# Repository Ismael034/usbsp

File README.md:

# USBsp

Have you ever tried to plug a USB device into a computer that has USB restrictions enabled? It's frustrating, isn't it? You can't use your USB devices, and you have no way to bypass the restrictions. But what if I told you that you could spoof the USB identifiers so you bypass these restrictions? That's where USBsp comes in.

Here is your solution!

USBsp is a USB device that can spoof the USB identifiers of any device you want. It is based on the CH32V203 and CH572D microcontrollers. With USBsp, you can easily bypass USB restrictions and use your USB devices without any issues.

## Features

- Spoofs basic USB descriptor fields: VID, PID, bcdDevice, manufacturer, product and serial.
- Stores the spoofed descriptor settings in EEPROM.
- WebUSB control panel for changing settings from a Chromium-based browser.
- Can read descriptor-like values from the currently connected downstream USB device and use them as a starting point.
- Basic live packet capture.
- Simple HID keyboard/mouse visualizers.

## Building

The required toolchain is alredy included. It is a custom toolchain made by WCH, downloaded from [here](https://www.mounriver.com/download). This toolchain constains custom targets for their MCUs. Other toolchains (like xpack) have not been tested.

### Clone the repository and add the toolchain to the path

```
git clone https://github.com/Ismael034/usbsp.git
cd usbsp
export PATH=$PWD/toolchain/bin/:$PATH
```

### Configure meson

```
meson setup build-ch32v203 --cross-file ch32v203/ch32v203-cross.ini
meson setup build-ch572d --cross-file ch572d/ch572d-cross.ini
```

### Build with ninja

```
ninja -C build-ch32v203 ch32v203/ch32v203.hex
ninja -C build-ch572d ch572d/ch572d.hex
```

If everything goes well, you'll end up with two .hex files – one for each MCU.

## Flashing

To flash the firmware to your MCU, you can use one of the following tools:

- [WCH-LinkUtility](https://www.wch.cn/downloads/wch-linkutility_zip.html)
- [wlink](https://github.com/ch32-rs/wlink/)
- [OpenOCD](https://openocd.org/)

```
wlink flash ./build-ch32v203/ch32v203/ch32v203.hex
wlink flash ./build-ch572d/ch572d/ch572d.hex
```

## Tests

It is also possible to build a test firmware, which will test hardware funcionality like EEPROM access, USBD, USBH, buttons, etc. You can build it using a predefined custom target.

```
ninja -C build-ch32v203 ch32v203/ch32v203_test.hex
```

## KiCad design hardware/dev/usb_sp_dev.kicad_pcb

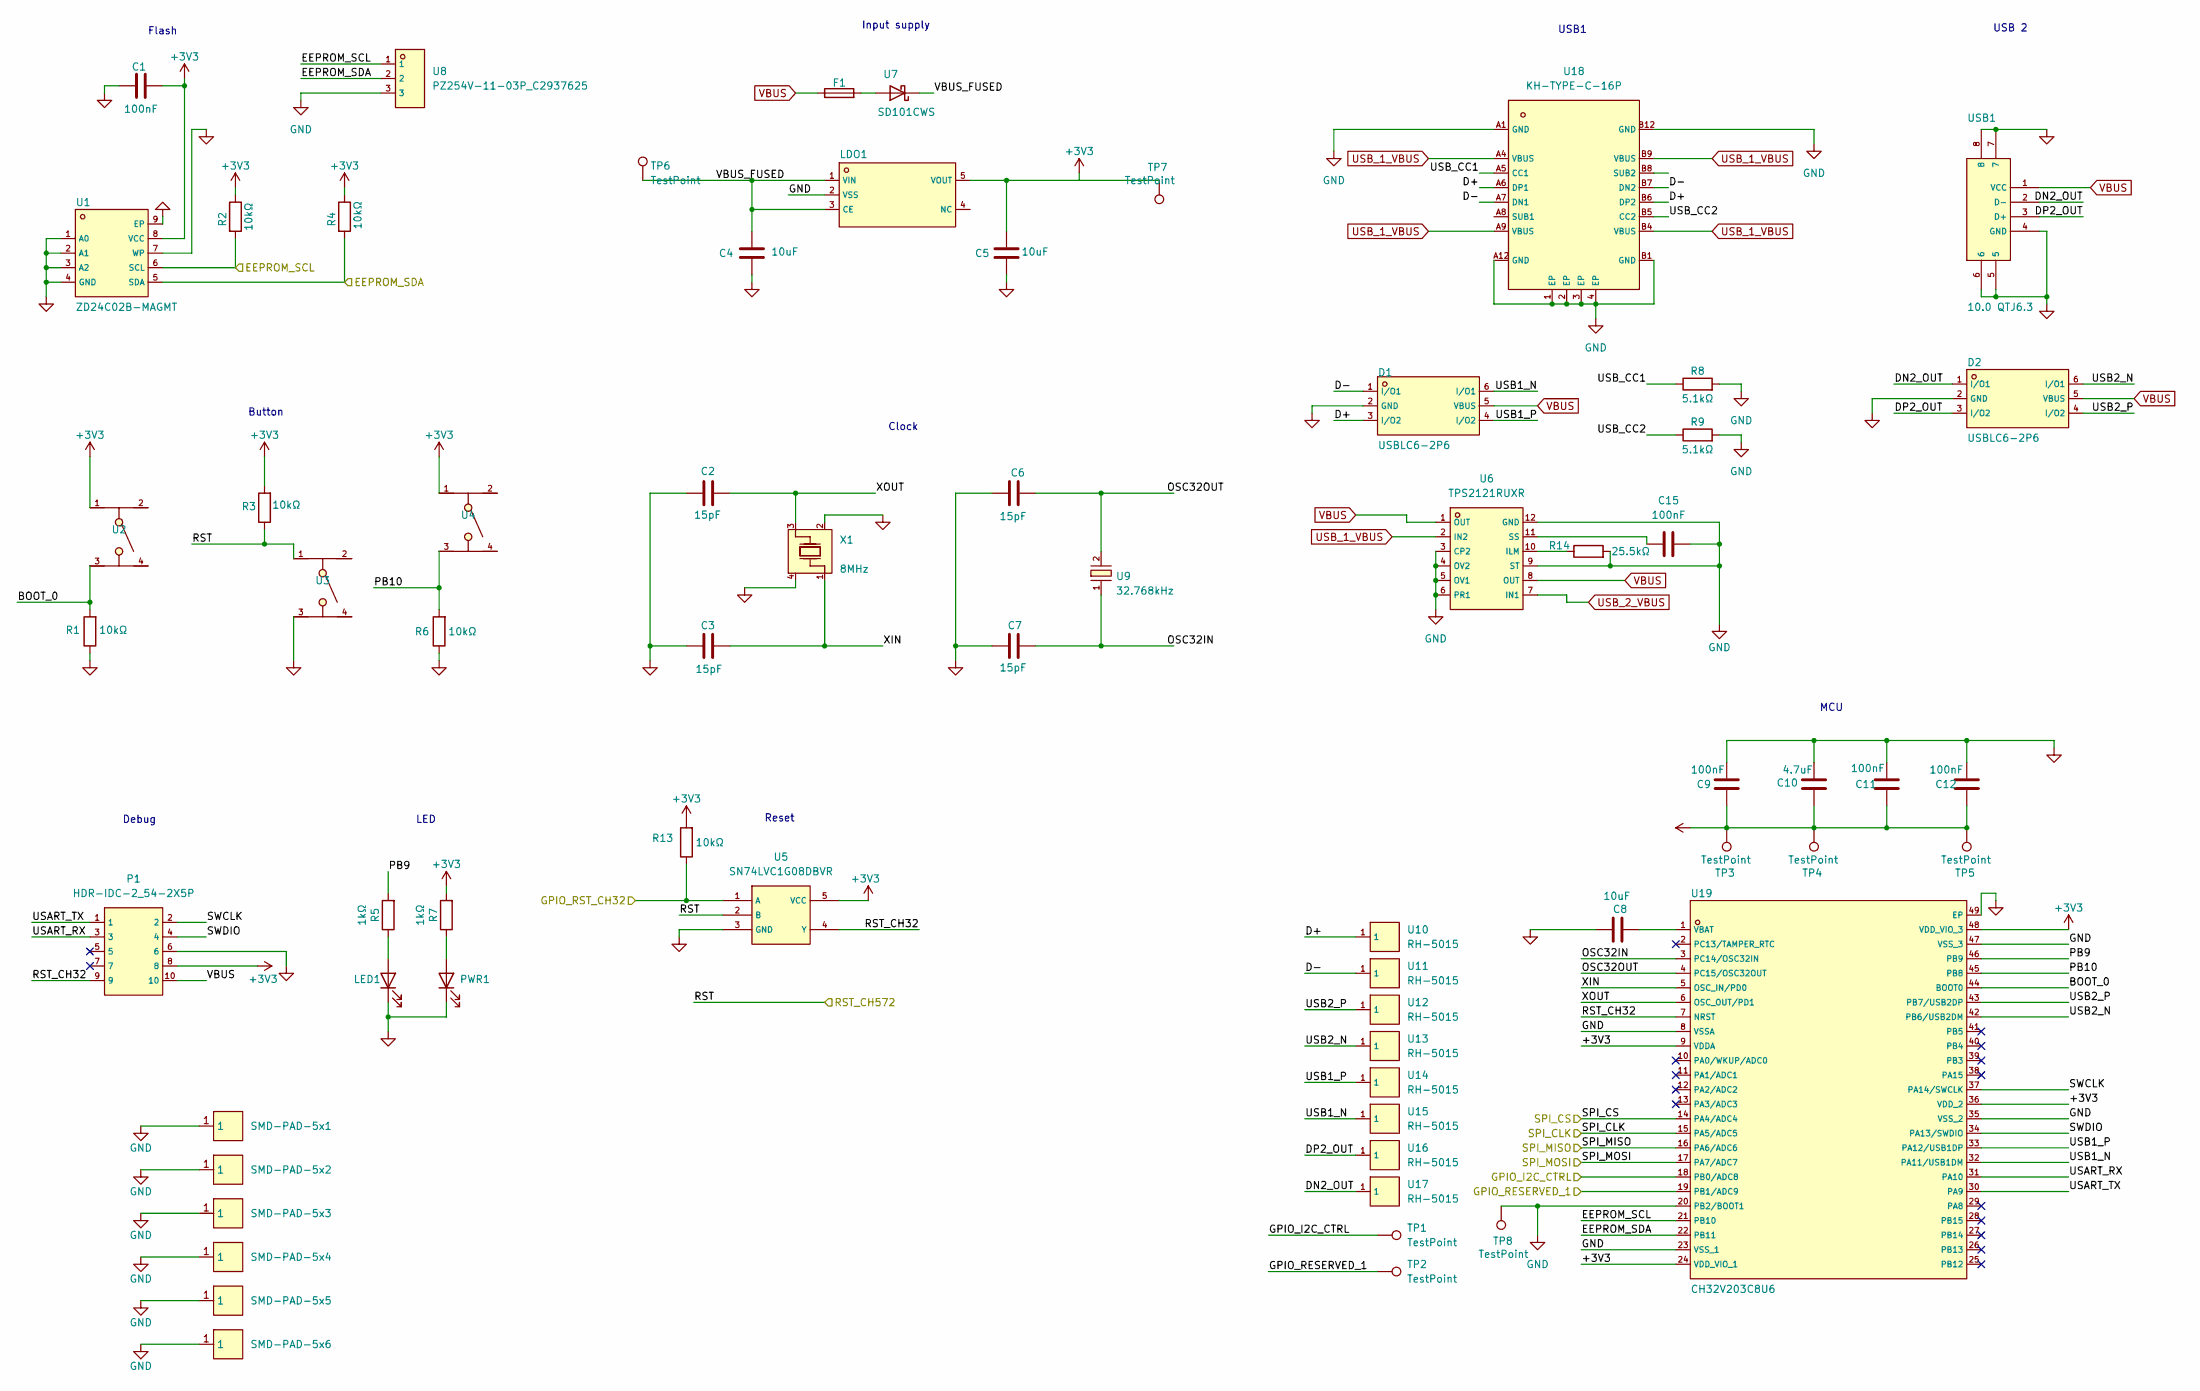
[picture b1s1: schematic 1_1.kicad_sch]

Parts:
C1: 100nF; C_0402_1005Metric; Manufacturer Part CL05B104KO5NNNC; LCSC Part Name 100nF ±10% 16V
C2, C3, C6, C7: 15pF; C_0402_1005Metric; Manufacturer Part 0402CG150J500NT; LCSC Part Name 15pF ±5% 50V
C4, C5, C8: 10uF; C_0603_1608Metric; Voltage Rating 10V; Manufacturer Part CGA0603X5R106K100JT; LCSC Part Name 10uF ±10% 10V
C9, C11, C12: 100nF; C_0603_1608Metric; Manufacturer Part CGA0603X7R104K500JT; LCSC Part Name 100nF ±10% 50V
C10: 4.7uF; C_0603_1608Metric; Manufacturer Part CL10A475KP8NNNC; LCSC Part Name 4.7uF ±10% 10V
C15: 100nF; C_0603_1608Metric
D1, D2: USBLC6-2P6; SOT-666-6_L1.6-W1.2-P0.50-LS1.6-BL; Manufacturer Part USBLC6-2P6; LCSC Part Name MSL=3
F1: JK-SMD0805-020-30V; Fuse_0805_2012Metric; Manufacturer Part JK-SMD0805-020-30V; LCSC Part Name 30V 200mA 0805自恢复
LDO1: ME6211C33M5G-N; SOT-23-5_L3.0-W1.7-P0.95-LS2.8-BL; Manufacturer Part ME6211C33M5G-N; LCSC Part Name 输入6V 输出3.3V 500mA
LED1: XL-1608UGC-04; LED_0603_1608Metric; Manufacturer Part XL-1608UGC-04; LCSC Part Name XL-1608UGC-04
P1: HDR-IDC-2_54-2X5P; IDC-TH_10P-P2.54_C5665; LCSC C5665
PWR1: NCD0603R1; LED_0603_1608Metric; Manufacturer Part NCD0603R1; LCSC Part Name NCD0603R1
R1, R2, R3, R4, R6, R13: 10kΩ; R_0603_1608Metric; Manufacturer Part RC0603JR-0710KL; LCSC Part Name 厚膜电阻 10kΩ ±5% 100mW
R5, R7: 1kΩ; R_0603_1608Metric
R8, R9: 5.1kΩ; R_0603_1608Metric
R14: 25.5kΩ; R_0603_1608Metric
SMD-PAD-5x1, SMD-PAD-5x2, SMD-PAD-5x3, SMD-PAD-5x4, SMD-PAD-5x5, SMD-PAD-5x6: SMD-PAD-5x5
TP1, TP2, TP3, TP4, TP5, TP6, TP7, TP8: TestPoint; TestPoint_Pad_D1.0mm
U1: ZD24C02B-MAGMT; UDFN-8_L3.0-W2.0-P0.50-BL-EP-3; Manufacturer Part ZD24C02B-MAGMT; LCSC Part Name 2Kbit I2C兼容串行EEPROM
U2, U3, U4: TC-6601-5_0-260-8_3; SW-SMD_4P-L6.0-W6.0-P4.50-LS8.2; Manufacturer Part TS-1088-AR02016; LCSC Part Name 4*3*2mm 立贴 轻触开关
U5: SN74LVC1G08DBVR; SOT-23-5_L3.0-W1.7-P0.95-LS2.8-BR; LCSC C7666
U6: TPS2121RUXR; VQFN-HR-12_L2.5-W2.0-P0.50-BL; LCSC C485916
U7: SD101CWS; D_SOD-323; Manufacturer Part SD101CWS; LCSC Part Name SD101CWS
U8: PZ254V-11-03P_C2937625; HDR-TH_3P-P2.54-V-M; LCSC C2937625
U9: 32.768kHz; CRYSTAL-SMD_L3.2-W1.5-1; Manufacturer Part H31003271C2070CY; LCSC Part Name 32.768kHz ±20ppm 12.5pF
U10, U11, U12, U13, U14, U15, U16, U17: RH-5015; SMD_RH-5015; LCSC C5199798
U18: KH-TYPE-C-16P; USB-C-SMD_KH-TYPE-C-16P; LCSC C709357
U19: CH32V203C8U6; TQFN-48_L7.0-W7.0-P0.50-BL-EP5.5; Manufacturer Part CH32V203C8U6; LCSC Part Name CH32V203C8U6
USB1: 10.0 QTJ6.3; USB-A-SMD_10.0-QTJ6.3; Manufacturer Part 10.0 QTJ6.3; LCSC Part Name Type-A 母 卧贴
X1: 8MHz; CRYSTAL-SMD_4P-L3.2-W2.5-BL; Manufacturer Part TAXM8M4RDBCCT2T; LCSC Part Name 8MHz ±10ppm 10pF

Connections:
+3V3: C1.1, C5.2, C9.1, C10.1, C11.1, C12.1, LDO1.5 (VOUT), P1.8, R2.1, R3.2, R4.1, R7.2, R13.2, TP3.1 (1_1), TP4.1 (1_1), TP5.1 (1_1), TP7.1 (1_1), U1.8 (VCC), U2.1, U4.1, U5.5 (VCC), U19.9 (VDDA), U19.24 (VDD_VIO_1), U19.36 (VDD_2), U19.48 (VDD_VIO_3); also elsewhere on the board
/CH32V203/BOOT_0: R1.2, U2.3, U19.44 (BOOT0)
/CH32V203/D+: D1.3 (I/O2), U10.1 (1_1), U18.A6 (DP1), U18.B6 (DP2)
/CH32V203/D-: D1.1 (I/O1), U11.1 (1_1), U18.A7 (DN1), U18.B7 (DN2)
/CH32V203/DN2_OUT: D2.1 (I/O1), U17.1 (1_1), USB1.2 (D-)
/CH32V203/DP2_OUT: D2.3 (I/O2), U16.1 (1_1), USB1.3 (D+)
/CH32V203/EEPROM_SCL: R2.2, U1.6 (SCL), U8.1, U19.21 (PB10); also elsewhere on the board
/CH32V203/EEPROM_SDA: R4.2, U1.5 (SDA), U8.2, U19.22 (PB11); also elsewhere on the board
/CH32V203/GPIO_I2C_CTRL: TP1.1 (1_1), U19.18 (PB0/ADC8); also elsewhere on the board
/CH32V203/GPIO_RESERVED_1: TP2.1 (1_1), U19.19 (PB1/ADC9); also elsewhere on the board
/CH32V203/GPIO_RST_CH32: R13.1, U5.1 (A); also elsewhere on the board
/CH32V203/OSC32IN: C7.2, U9.1, U19.3 (PC14/OSC32IN)
/CH32V203/OSC32OUT: C6.1, U9.2, U19.4 (PC15/OSC32OUT)
/CH32V203/PB9: R5.2, U19.46 (PB9)
/CH32V203/PB10: R6.2, U4.3, U19.45 (PB8)
/CH32V203/RST: R3.1, U3.1, U5.2 (B); also elsewhere on the board
/CH32V203/RST_CH32: P1.9, U5.4 (Y), U19.7 (NRST)
/CH32V203/SPI_CLK: U19.15 (PA5/ADC5); also elsewhere on the board
/CH32V203/SPI_CS: U19.14 (PA4/ADC4); also elsewhere on the board
/CH32V203/SPI_MISO: U19.16 (PA6/ADC6); also elsewhere on the board
/CH32V203/SPI_MOSI: U19.17 (PA7/ADC7); also elsewhere on the board
/CH32V203/SWCLK: P1.2, U19.37 (PA14/SWCLK)
/CH32V203/SWDIO: P1.4, U19.34 (PA13/SWDIO)
/CH32V203/USART_RX: P1.3, U19.31 (PA10)
/CH32V203/USART_TX: P1.1, U19.30 (PA9)
/CH32V203/USB1_N: D1.6 (I/O1), U15.1 (1_1), U19.32 (PA11/USB1DM)
/CH32V203/USB1_P: D1.4 (I/O2), U14.1 (1_1), U19.33 (PA12/USB1DP)
/CH32V203/USB2_N: D2.6 (I/O1), U13.1 (1_1), U19.42 (PB6/USB2DM)
/CH32V203/USB2_P: D2.4 (I/O2), U12.1 (1_1), U19.43 (PB7/USB2DP)
/CH32V203/USB_CC1: R8.1, U18.A5 (CC1)
/CH32V203/USB_CC2: R9.1, U18.B5 (CC2)
/CH32V203/VBUS_FUSED: C4.2, LDO1.1 (VIN), LDO1.3 (CE), TP6.1 (1_1), U7.1 (K)
/CH32V203/XIN: C3.2, U19.5 (OSC_IN/PD0), X1.1
/CH32V203/XOUT: C2.1, U19.6 (OSC_OUT/PD1), X1.3
GND: C1.2, C2.2, C3.1, C4.1, C5.1, C6.2, C7.1, C8.2, C9.2, C10.2, C11.2, C12.2, C15.2, D1.2 (GND), D2.2 (GND), LDO1.2 (VSS), LED1.1 (K), P1.6, PWR1.1 (K), R1.1, R6.1, R8.2, R9.2, R14.2, SMD-PAD-5x1.1 (1_1), SMD-PAD-5x2.1 (1_1), SMD-PAD-5x3.1 (1_1), SMD-PAD-5x4.1 (1_1), SMD-PAD-5x5.1 (1_1), SMD-PAD-5x6.1 (1_1), TP8.1 (1_1), U1.1 (A0), U1.2 (A1), U1.3 (A2), U1.4 (GND), U1.7 (WP), U1.9 (EP), U3.3, U5.3 (GND), U6.3 (CP2), U6.4 (OV2), U6.5 (OV1), U6.6 (PR1), U6.9 (ST), U6.12 (GND), U8.3, U18.1 (EP), U18.2 (EP), U18.3 (EP), U18.4 (EP), U18.A1 (GND), U18.A12 (GND), U18.B1 (GND), U18.B12 (GND), U19.8 (VSSA), U19.20 (PB2/BOOT1), U19.23 (VSS_1), U19.35 (VSS_2), U19.47 (VSS_3), U19.49 (EP), USB1.4 (GND), USB1.5, USB1.6, USB1.7, USB1.8, X1.2, X1.4; also elsewhere on the board
unnamed: LED1.2 (A), R5.1
unnamed: PWR1.2 (A), R7.1
unnamed: R14.1, U6.10 (ILM)
unnamed: C15.1, U6.11 (SS)
unnamed: F1.2, U7.2 (A)
unnamed: C8.1, U19.1 (VBAT)
USB_1_VBUS: U6.2 (IN2), U18.A4 (VBUS), U18.A9 (VBUS), U18.B4 (VBUS), U18.B9 (VBUS)
USB_2_VBUS: U6.7 (IN1); also elsewhere on the board
VBUS: D1.5 (VBUS), D2.5 (VBUS), F1.1, P1.10, U6.1 (OUT), U6.8 (OUT), USB1.1 (VCC); also elsewhere on the board

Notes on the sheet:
Reset
Debug
Clock
Button
USB1
Flash
Input supply
USB 2
LED
MCU

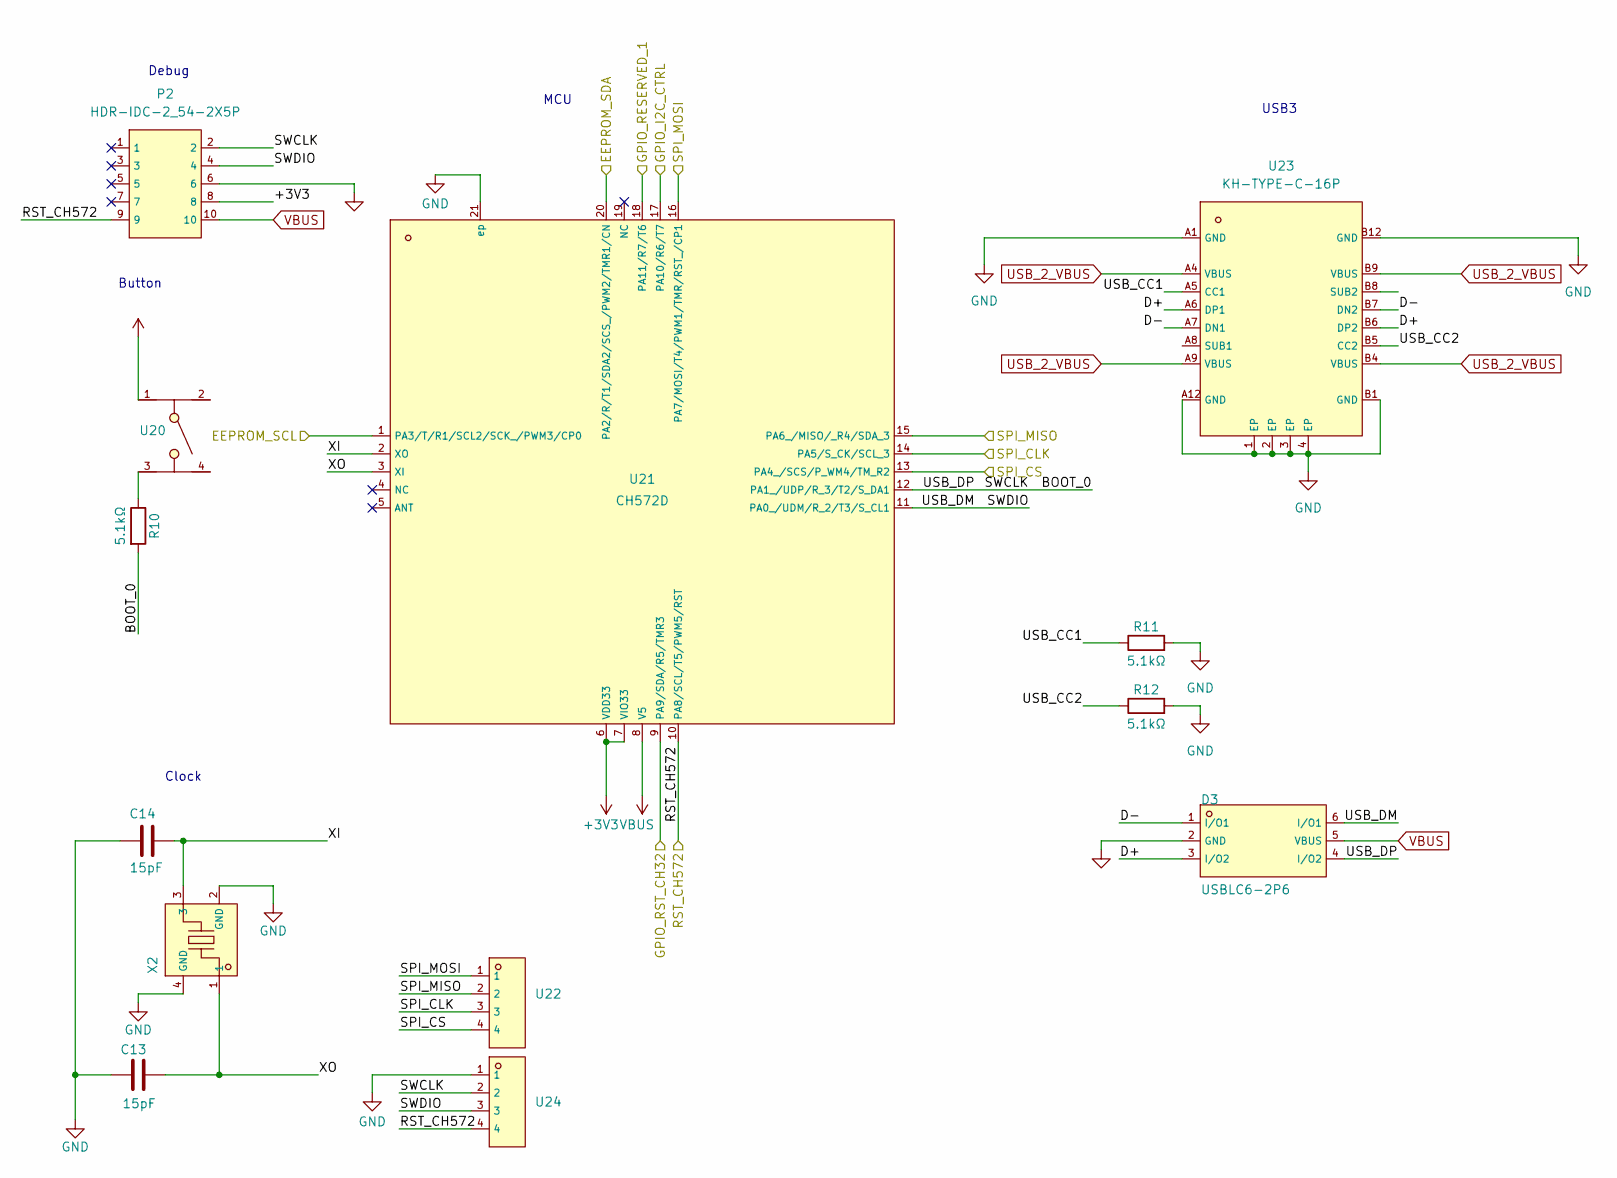
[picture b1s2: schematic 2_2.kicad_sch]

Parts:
C13, C14: 15pF; C_0402_1005Metric; Manufacturer Part 0402CG150J500NT; LCSC Part Name 15pF ±5% 50V
D3: USBLC6-2P6; SOT-666-6_L1.6-W1.2-P0.50-LS1.6-BL; Manufacturer Part USBLC6-2P6; LCSC Part Name MSL=3
P2: HDR-IDC-2_54-2X5P; IDC-TH_10P-P2.54_C5665; LCSC C5665
R10, R11, R12: 5.1kΩ; R_0603_1608Metric
U20: TC-6601-5_0-260-8_3; SW-SMD_4P-L6.0-W6.0-P4.50-LS8.2; Manufacturer Part TS-1088-AR02016; LCSC Part Name 4*3*2mm 立贴 轻触开关
U21: CH572D; QFN-20_L3.0-W3.0-P0.40-TL-EP1.7; LCSC C46597863
U22, U24: HX_PH254-01-04-Z-L11_5_STRAIGHT_PIN_HEADER; HDR-TH_4P-HX-PH254-01-04-Z-L11.5; LCSC C52016392
U23: KH-TYPE-C-16P; USB-C-SMD_KH-TYPE-C-16P; LCSC C709357
X2: XTM20032000DT00351001; CRYSTAL-SMD_4P-L2.0-W1.6-BL; LCSC C37635331

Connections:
+3V3: P2.8, U20.1, U21.6 (VDD33), U21.7 (VIO33); also elsewhere on the board
/CH32V203/EEPROM_SCL: U21.1 (PA3/T/R1/SCL2/SCK_/PWM3/CP0); also elsewhere on the board
/CH32V203/EEPROM_SDA: U21.20 (PA2/R/T1/SDA2/SCS_/PWM2/TMR1/CN); also elsewhere on the board
/CH32V203/GPIO_I2C_CTRL: U21.17 (PA10/R6/T7); also elsewhere on the board
/CH32V203/GPIO_RESERVED_1: U21.18 (PA11/R7/T6); also elsewhere on the board
/CH32V203/GPIO_RST_CH32: U21.9 (PA9/SDA/R5/TMR3); also elsewhere on the board
/CH32V203/RST: P2.9, U21.10 (PA8/SCL/T5/PWM5/RST), U24.4; also elsewhere on the board
/CH32V203/SPI_CLK: U21.14 (PA5/S_CK/SCL_3), U22.3; also elsewhere on the board
/CH32V203/SPI_CS: U21.13 (PA4_/SCS/P_WM4/TM_R2), U22.4; also elsewhere on the board
/CH32V203/SPI_MISO: U21.15 (PA6_/MISO/_R4/SDA_3), U22.2; also elsewhere on the board
/CH32V203/SPI_MOSI: U21.16 (PA7/MOSI/T4/PWM1/TMR/RST_/CP1), U22.1; also elsewhere on the board
/CH572D/BOOT_0: D3.4 (I/O2), P2.2, R10.2, U21.12 (PA1_/UDP/R_3/T2/S_DA1), U24.2
/CH572D/D+: D3.3 (I/O2), U23.A6 (DP1), U23.B6 (DP2)
/CH572D/D-: D3.1 (I/O1), U23.A7 (DN1), U23.B7 (DN2)
/CH572D/SWDIO: D3.6 (I/O1), P2.4, U21.11 (PA0_/UDM/R_2/T3/S_CL1), U24.3
/CH572D/USB_CC1: R11.1, U23.A5 (CC1)
/CH572D/USB_CC2: R12.1, U23.B5 (CC2)
/CH572D/XI: C14.1, U21.2 (XO), X2.3
/CH572D/XO: C13.2, U21.3 (XI), X2.1
GND: C13.1, C14.2, D3.2 (GND), P2.6, R11.2, R12.2, U21.21 (ep), U23.1 (EP), U23.2 (EP), U23.3 (EP), U23.4 (EP), U23.A1 (GND), U23.A12 (GND), U23.B1 (GND), U23.B12 (GND), U24.1, X2.2 (GND), X2.4 (GND); also elsewhere on the board
unnamed: R10.1, U20.3
USB_2_VBUS: U23.A4 (VBUS), U23.A9 (VBUS), U23.B4 (VBUS), U23.B9 (VBUS); also elsewhere on the board
VBUS: D3.5 (VBUS), P2.10, U21.8 (V5); also elsewhere on the board

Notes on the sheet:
USB3
Button
Debug
MCU
Clock

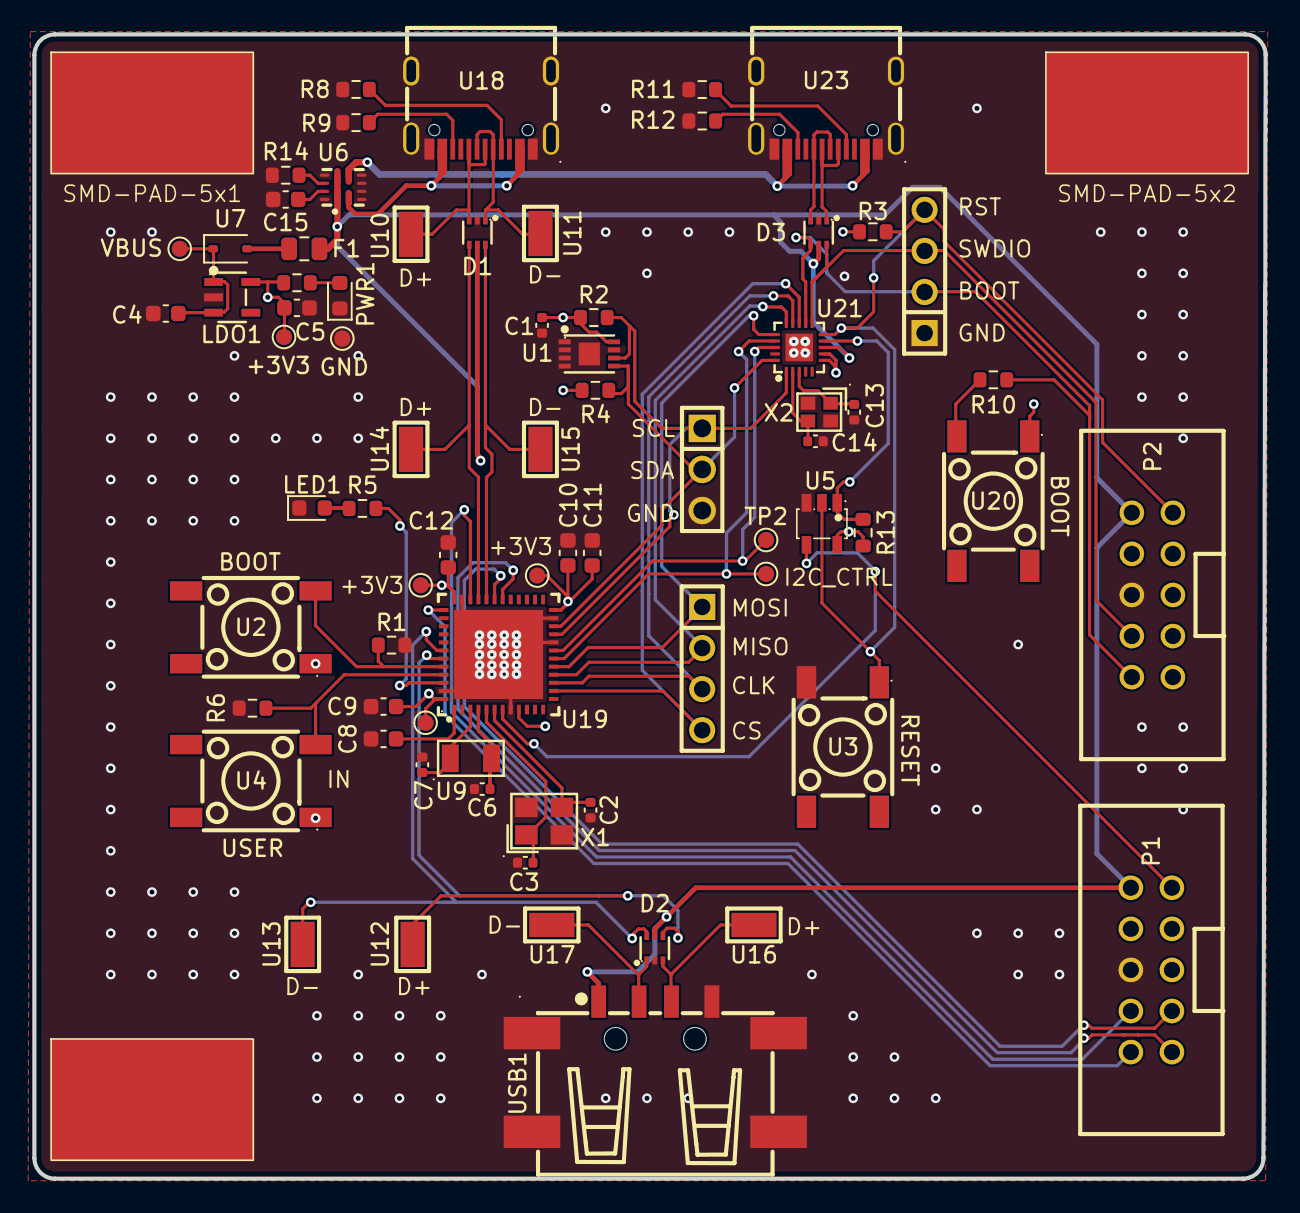
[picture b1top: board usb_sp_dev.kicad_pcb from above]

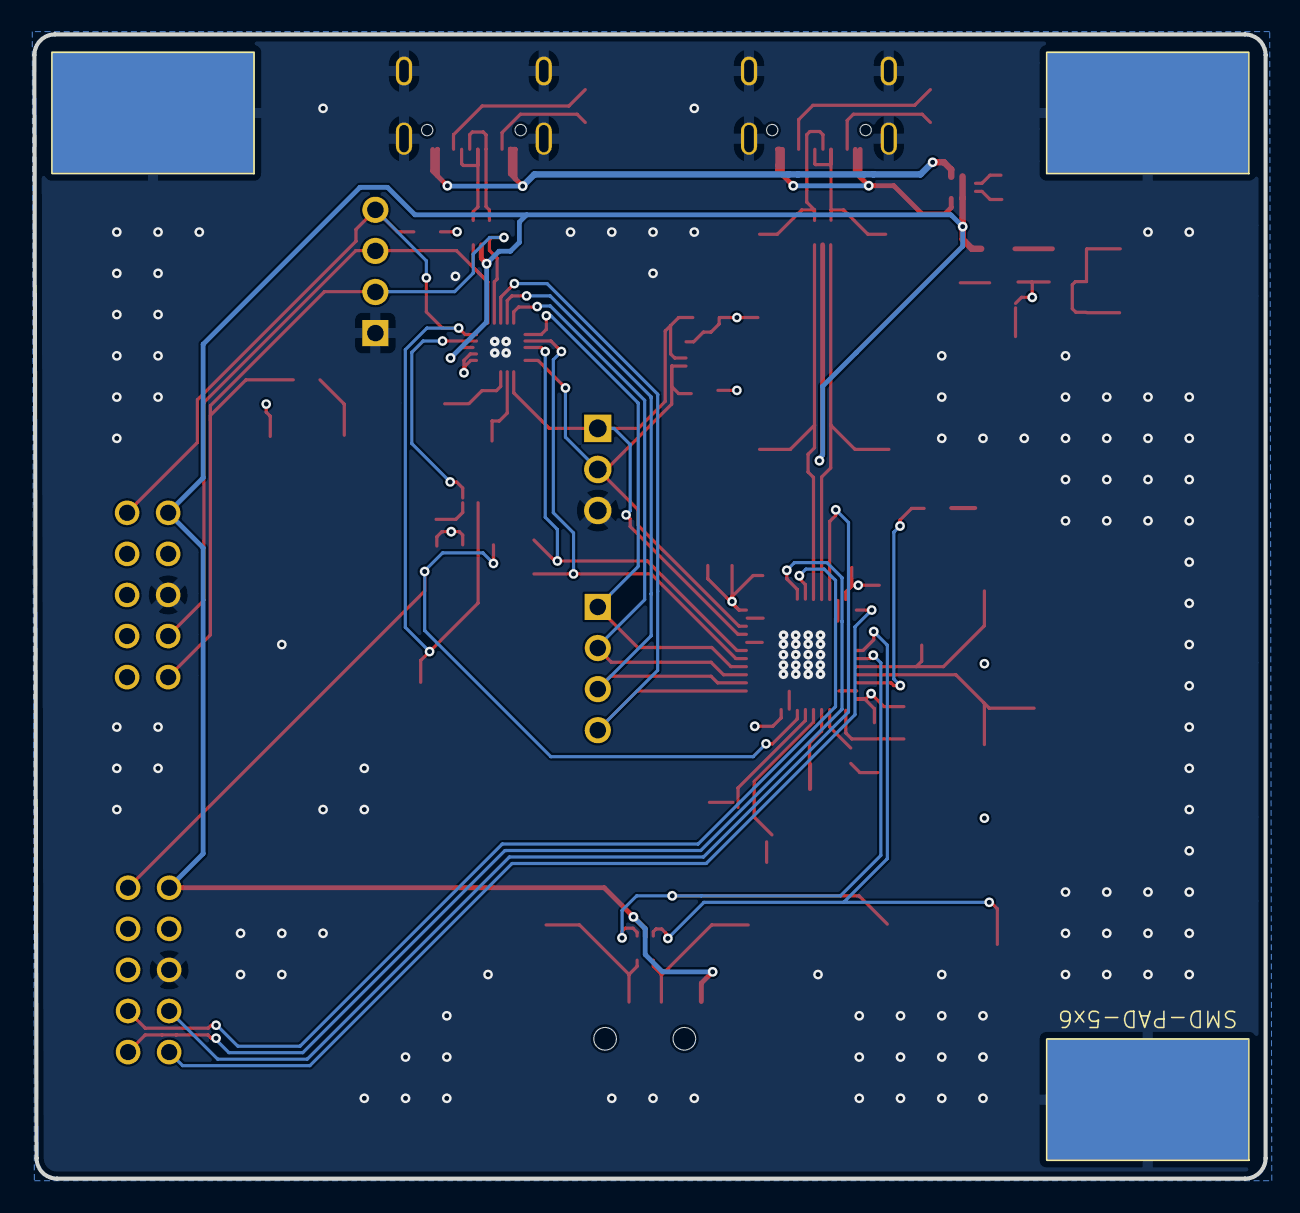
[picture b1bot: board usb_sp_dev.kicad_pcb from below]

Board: 4 copper layers, 76.1 x 70.7 mm, 79 parts (3 on the bottom side), 53 nets.

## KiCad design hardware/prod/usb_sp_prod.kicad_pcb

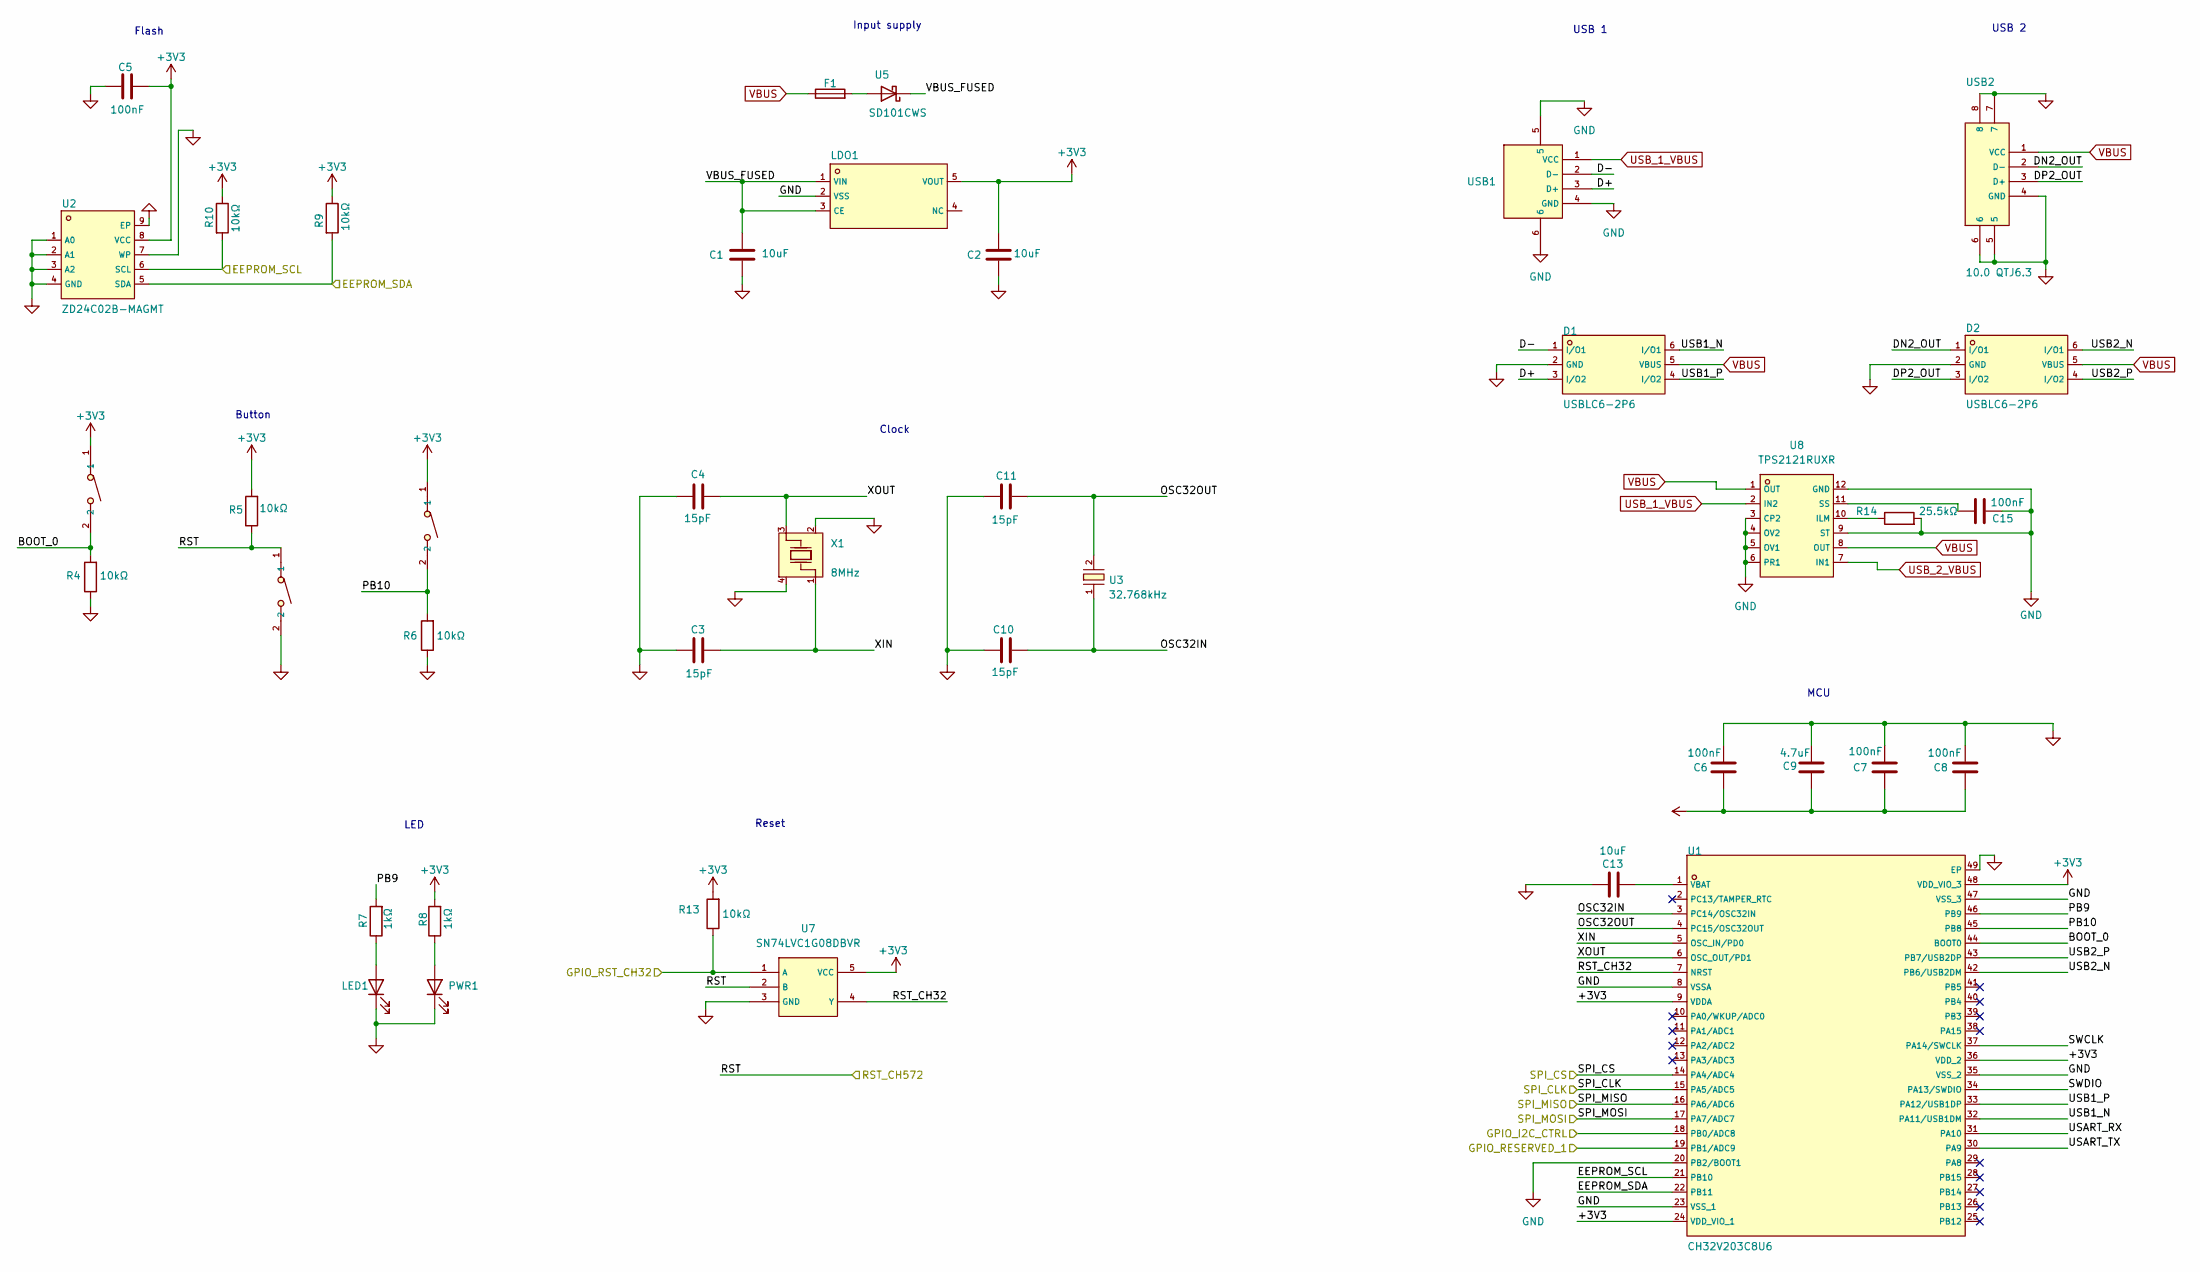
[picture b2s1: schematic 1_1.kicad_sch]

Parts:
C1, C2, C13: 10uF; C_0402_1005Metric; Voltage Rating 10V; Manufacturer Part CL05A106MP5NUNC; LCSC Part Name CAP CER 10uF 10V X5R 0402
C3, C4, C10, C11: 15pF; C_0402_1005Metric; Manufacturer Part 0402CG150J500NT; LCSC Part Name 15pF ±5% 50V
C5, C15: 100nF; C_0402_1005Metric; Manufacturer Part CL05B104KO5NNNC; LCSC Part Name 100nF ±10% 16V
C6, C7, C8: 100nF; C_0402_1005Metric; Manufacturer Part CC0402KRX7R7BB104; LCSC Part Name CAP CER 100nF 16V X7R 0402
C9: 4.7uF; C_0402_1005Metric; Manufacturer Part CL05A475KP5NRNC; LCSC Part Name 4.7uF ±10% 10V Ceramic Capacitor X5R 04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
D1, D2: USBLC6-2P6; SOT-666-6_L1.6-W1.2-P0.50-LS1.6-BL; Manufacturer Part USBLC6-2P6; LCSC Part Name MSL=3
F1: JK-SMD0805-020-30V; Fuse_0805_2012Metric; Manufacturer Part JK-SMD0805-020-30V; LCSC Part Name 30V 200mA 0805自恢复
LDO1: ME6211C33M5G-N; SOT-23-5_L3.0-W1.7-P0.95-LS2.8-BL; Manufacturer Part ME6211C33M5G-N; LCSC Part Name 输入6V 输出3.3V 500mA
LED1: XL-1608UGC-04; LED_0603_1608Metric; Manufacturer Part XL-1608UGC-04; LCSC Part Name XL-1608UGC-04
PWR1: NCD0603R1; LED_0603_1608Metric; Manufacturer Part NCD0603R1; LCSC Part Name NCD0603R1
R4, R5, R6, R9, R10, R13: 10kΩ; R_0402_1005Metric; Manufacturer Part RC0402FR-0710KL; LCSC Part Name RES 10kΩ ±1% 62.5mW 0402
R7, R8: 1kΩ; R_0402_1005Metric; Manufacturer Part 0402WGF1001TCE; LCSC Part Name 1kΩ ±1% 62.5mW 厚膜电阻
R14: 25.5kΩ; R_0402_1005Metric; Manufacturer Part RC0402FR-0710KL; LCSC Part Name RES 10kΩ ±1% 62.5mW 0402
RESET1, RESET2: SW-SMD_L3.9-W3.0-P4.45; Manufacturer Part TS-1088-AR02016; LCSC Part Name 4*3*2mm 立贴 轻触开关
U1: CH32V203C8U6; TQFN-48_L7.0-W7.0-P0.50-BL-EP5.5; Manufacturer Part CH32V203C8U6; LCSC Part Name CH32V203C8U6
U2: ZD24C02B-MAGMT; UDFN-8_L3.0-W2.0-P0.50-BL-EP-3; Manufacturer Part ZD24C02B-MAGMT; LCSC Part Name 2Kbit I2C兼容串行EEPROM
U3: 32.768kHz; CRYSTAL-SMD_L3.2-W1.5-1; Manufacturer Part H31003271C2070CY; LCSC Part Name 32.768kHz ±20ppm 12.5pF
U5: SD101CWS; D_SOD-323; Manufacturer Part SD101CWS; LCSC Part Name SD101CWS
U7: SN74LVC1G08DBVR; SOT-23-5_L3.0-W1.7-P0.95-LS2.8-BR; LCSC C7666
U8: TPS2121RUXR; VQFN-HR-12_L2.5-W2.0-P0.50-BL; LCSC C485916
USB1: USB-A-A/M_Stick_plate_bent_legs_VinylPBT_With_a_c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; USB-A-SMD_917-181A102ES60200; LCSC C46394
USB2: 10.0 QTJ6.3; USB-A-SMD_10.0-QTJ6.3; Manufacturer Part 10.0 QTJ6.3; LCSC Part Name Type-A 母 卧贴
USER1: SW-SMD_L3.9-W3.0-P4.45; Manufacturer Part TS-1088-AR02016; LCSC Part Name 4*3*2mm 立贴 轻触开关
X1: 8MHz; CRYSTAL-SMD_4P-L3.2-W2.5-BL; Manufacturer Part TAXM8M4RDBCCT2T; LCSC Part Name 8MHz ±10ppm 10pF

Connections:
+3V3: C2.2, C5.1, C6.1, C7.1, C8.1, C9.1, LDO1.5 (VOUT), R5.2, R8.2, R9.1, R10.1, R13.2, RESET2.1, U1.9 (VDDA), U1.24 (VDD_VIO_1), U1.36 (VDD_2), U1.48 (VDD_VIO_3), U2.8 (VCC), U7.5 (VCC), USER1.1; also elsewhere on the board
/CH32V203/BOOT_0: R4.2, RESET2.2, U1.44 (BOOT0)
/CH32V203/D+: D1.3 (I/O2), USB1.3 (D+)
/CH32V203/D-: D1.1 (I/O1), USB1.2 (D-)
/CH32V203/DN2_OUT: D2.1 (I/O1), USB2.2 (D-)
/CH32V203/DP2_OUT: D2.3 (I/O2), USB2.3 (D+)
/CH32V203/EEPROM_SCL: R10.2, U1.21 (PB10), U2.6 (SCL); also elsewhere on the board
/CH32V203/EEPROM_SDA: R9.2, U1.22 (PB11), U2.5 (SDA); also elsewhere on the board
/CH32V203/GPIO_I2C_CTRL: U1.18 (PB0/ADC8); also elsewhere on the board
/CH32V203/GPIO_RESERVED_1: U1.19 (PB1/ADC9); also elsewhere on the board
/CH32V203/GPIO_RST_CH32: R13.1, U7.1 (A); also elsewhere on the board
/CH32V203/OSC32IN: C10.2, U1.3 (PC14/OSC32IN), U3.1
/CH32V203/OSC32OUT: C11.1, U1.4 (PC15/OSC32OUT), U3.2
/CH32V203/PB9: R7.2, U1.46 (PB9)
/CH32V203/PB10: R6.2, U1.45 (PB8), USER1.2
/CH32V203/RST: R5.1, RESET1.1, U7.2 (B); also elsewhere on the board
/CH32V203/RST_CH32: U1.7 (NRST), U7.4 (Y)
/CH32V203/SPI_CLK: U1.15 (PA5/ADC5); also elsewhere on the board
/CH32V203/SPI_CS: U1.14 (PA4/ADC4); also elsewhere on the board
/CH32V203/SPI_MISO: U1.16 (PA6/ADC6); also elsewhere on the board
/CH32V203/SPI_MOSI: U1.17 (PA7/ADC7); also elsewhere on the board
/CH32V203/SWCLK: U1.37 (PA14/SWCLK); also elsewhere on the board
/CH32V203/SWDIO: U1.34 (PA13/SWDIO); also elsewhere on the board
/CH32V203/USART_RX: U1.31 (PA10)
/CH32V203/USART_TX: U1.30 (PA9)
/CH32V203/USB1_N: D1.6 (I/O1), U1.32 (PA11/USB1DM)
/CH32V203/USB1_P: D1.4 (I/O2), U1.33 (PA12/USB1DP)
/CH32V203/USB2_N: D2.6 (I/O1), U1.42 (PB6/USB2DM)
/CH32V203/USB2_P: D2.4 (I/O2), U1.43 (PB7/USB2DP)
/CH32V203/VBUS_FUSED: C1.2, LDO1.1 (VIN), LDO1.3 (CE), U5.1 (K)
/CH32V203/XIN: C3.2, U1.5 (OSC_IN/PD0), X1.1
/CH32V203/XOUT: C4.1, U1.6 (OSC_OUT/PD1), X1.3
GND: C1.1, C2.1, C3.1, C4.2, C5.2, C6.2, C7.2, C8.2, C9.2, C10.1, C11.2, C13.2, C15.2, D1.2 (GND), D2.2 (GND), LDO1.2 (VSS), LED1.1 (K), PWR1.1 (K), R4.1, R6.1, R14.2, RESET1.2, U1.8 (VSSA), U1.20 (PB2/BOOT1), U1.23 (VSS_1), U1.35 (VSS_2), U1.47 (VSS_3), U1.49 (EP), U2.1 (A0), U2.2 (A1), U2.3 (A2), U2.4 (GND), U2.7 (WP), U2.9 (EP), U7.3 (GND), U8.3 (CP2), U8.4 (OV2), U8.5 (OV1), U8.6 (PR1), U8.9 (ST), U8.12 (GND), USB1.4 (GND), USB1.5, USB1.6, USB2.4 (GND), USB2.5, USB2.6, USB2.7, USB2.8, X1.2, X1.4; also elsewhere on the board
unnamed: LED1.2 (A), R7.1
unnamed: PWR1.2 (A), R8.1
unnamed: C13.1, U1.1 (VBAT)
unnamed: F1.2, U5.2 (A)
unnamed: R14.1, U8.10 (ILM)
unnamed: C15.1, U8.11 (SS)
USB_1_VBUS: U8.2 (IN2), USB1.1 (VCC)
USB_2_VBUS: U8.7 (IN1); also elsewhere on the board
VBUS: D1.5 (VBUS), D2.5 (VBUS), F1.1, U8.1 (OUT), U8.8 (OUT), USB2.1 (VCC)

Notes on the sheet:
Reset
Clock
Button
Flash
Input supply
USB 1
USB 2
LED
MCU
